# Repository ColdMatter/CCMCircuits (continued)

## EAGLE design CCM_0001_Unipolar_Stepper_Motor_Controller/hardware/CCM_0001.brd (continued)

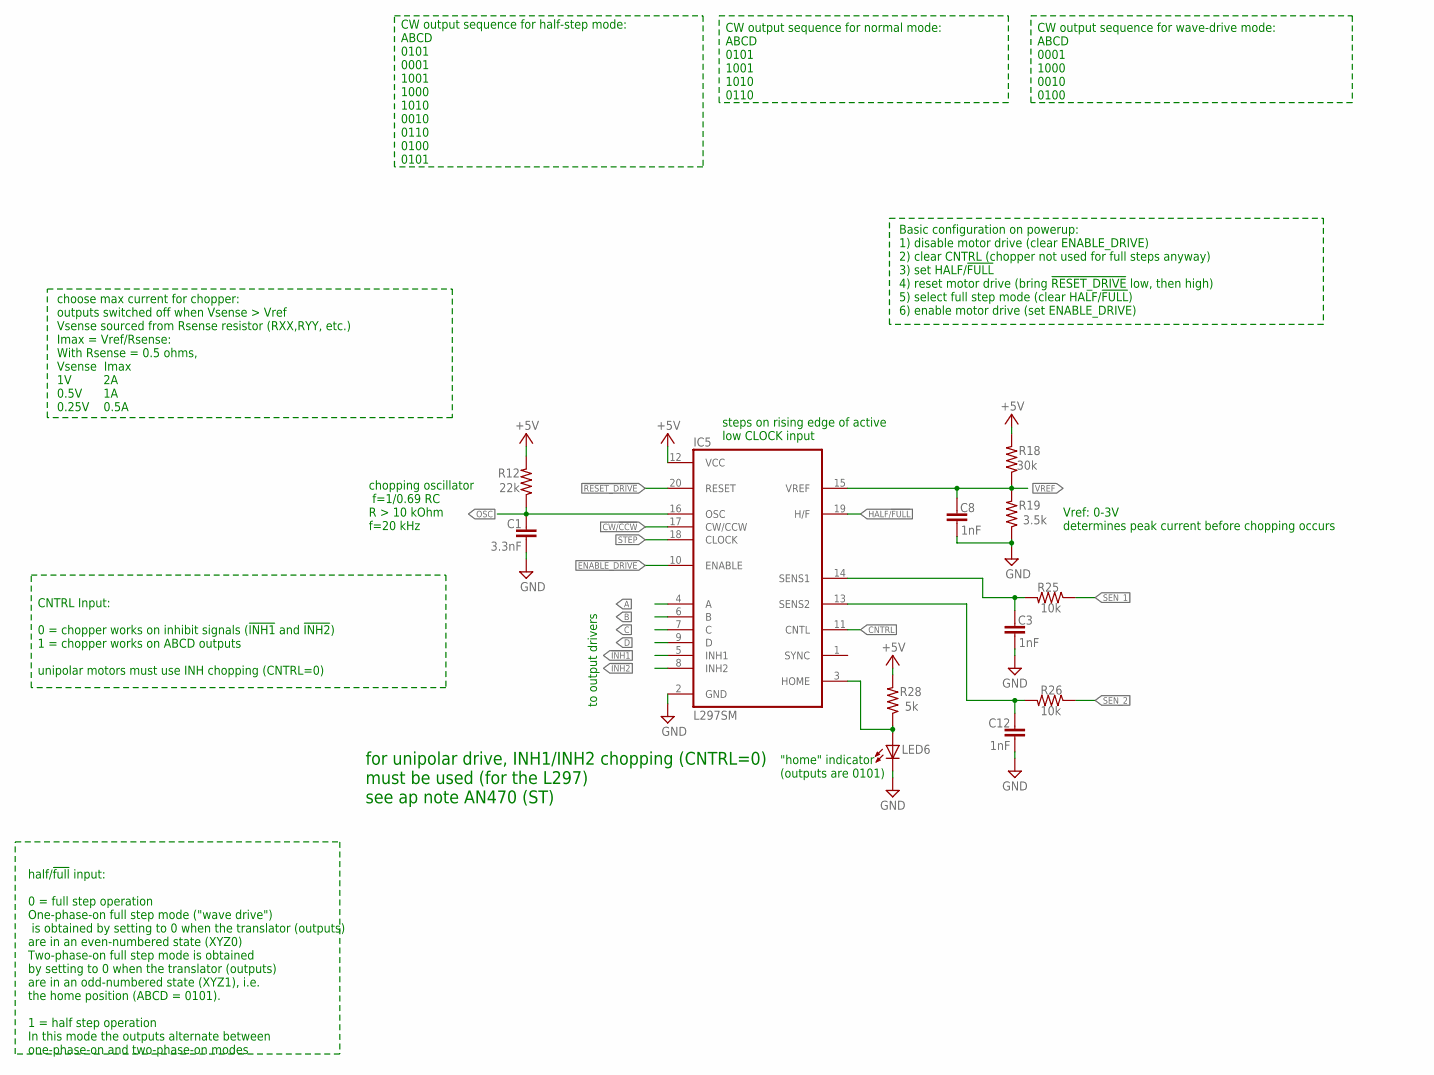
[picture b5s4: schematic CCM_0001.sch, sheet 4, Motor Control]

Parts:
C1: 3.3nF; 0603-CAP
C3, C8, C12: 1nF; 0603-CAP
IC5: L297SM; SO20
LED6: red; CHIPLED_0603
R12: 22k; 0603-RES
R18: 30k; 0603-RES
R19: 3.5k; 0603-RES
R25, R26: 10k; 0603-RES
R28: 5k; 0603-RES

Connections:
!INH1: IC5.5 (INH1); also elsewhere on the board
!INH2: IC5.8 (INH2); also elsewhere on the board
!RESET_DRIVE: IC5.20 (RESET); also elsewhere on the board
+5V: IC5.12 (VCC), R12.2, R18.2, R28.2; also elsewhere on the board
A: IC5.4 (A); also elsewhere on the board
B: IC5.6 (B); also elsewhere on the board
C: IC5.7 (C); also elsewhere on the board
CNTRL: IC5.11 (CNTL); also elsewhere on the board
CW/!CCW: IC5.17 (CW/CCW); also elsewhere on the board
D: IC5.9 (D); also elsewhere on the board
ENABLE_DRIVE: IC5.10 (ENABLE); also elsewhere on the board
GND: C1.2, C3.2, C8.2, C12.2, IC5.2 (GND), LED6.C, R19.1; also elsewhere on the board
HALF/!FULL: IC5.19 (H/F); also elsewhere on the board
unnamed: IC5.3 (HOME), LED6.A, R28.1
OSC: C1.1, IC5.16 (OSC), R12.1
SENSE1: C3.1, IC5.14 (SENS1), R25.2
SENSE2: C12.1, IC5.13 (SENS2), R26.2
SEN_1: R25.1; also elsewhere on the board
SEN_2: R26.1; also elsewhere on the board
STEP: IC5.18 (CLOCK); also elsewhere on the board
VREF: C8.1, IC5.15 (VREF), R18.1, R19.2

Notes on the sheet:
chopping oscillator f=1/0.69 RC R > 10 kOhm f=20 kHz
steps on rising edge of active low CLOCK input
choose max current for chopper: outputs switched off when Vsense > Vref Vsense sourced from Rsense resistor (RXX,RYY, etc.) Imax = Vref/Rsense: With Rsense = 0.5 ohms, Vsense Imax 1V 2A 0.5V 1A 0.25V 0.5A
"home" indicator (outputs are 0101)
to output drivers
CNTRL Input: 0 = chopper works on inhibit signals (!INH1! and !INH2!) 1 = chopper works on ABCD outputs unipolar motors must use INH chopping (CNTRL=0)
half/!full! input: 0 = full step operation One-phase-on full step mode ("wave drive") is obtained by setting to 0 when the translator (outputs) are in an even-numbered state (XYZ0) Two-phase-on full step mode is obtained by setting to 0 when the translator (outputs) are in an odd-numbered state (XY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
CW output sequence for half-step mode: ABCD 0101 0001 1001 1000 1010 0010 0110 0100 0101
Basic configuration on powerup: 1) disable motor drive (clear ENABLE_DRIVE) 2) clear CNTRL (chopper not used for full steps anyway) 3) set HALF/!FULL! 4) reset motor drive (bring !RESET_DRIVE! low, then high) 5) select full step mode (clear HALF/!FULL!) 6) enable motor drive (set ENABLE_DRIVE)
CW output sequence for normal mode: ABCD 0101 1001 1010 0110
CW output sequence for wave-drive mode: ABCD 0001 1000 0010 0100
Vref: 0-3V determines peak current before chopping occurs
for unipolar drive, INH1/INH2 chopping (CNTRL=0) must be used (for the L297) see ap note AN470 (ST)

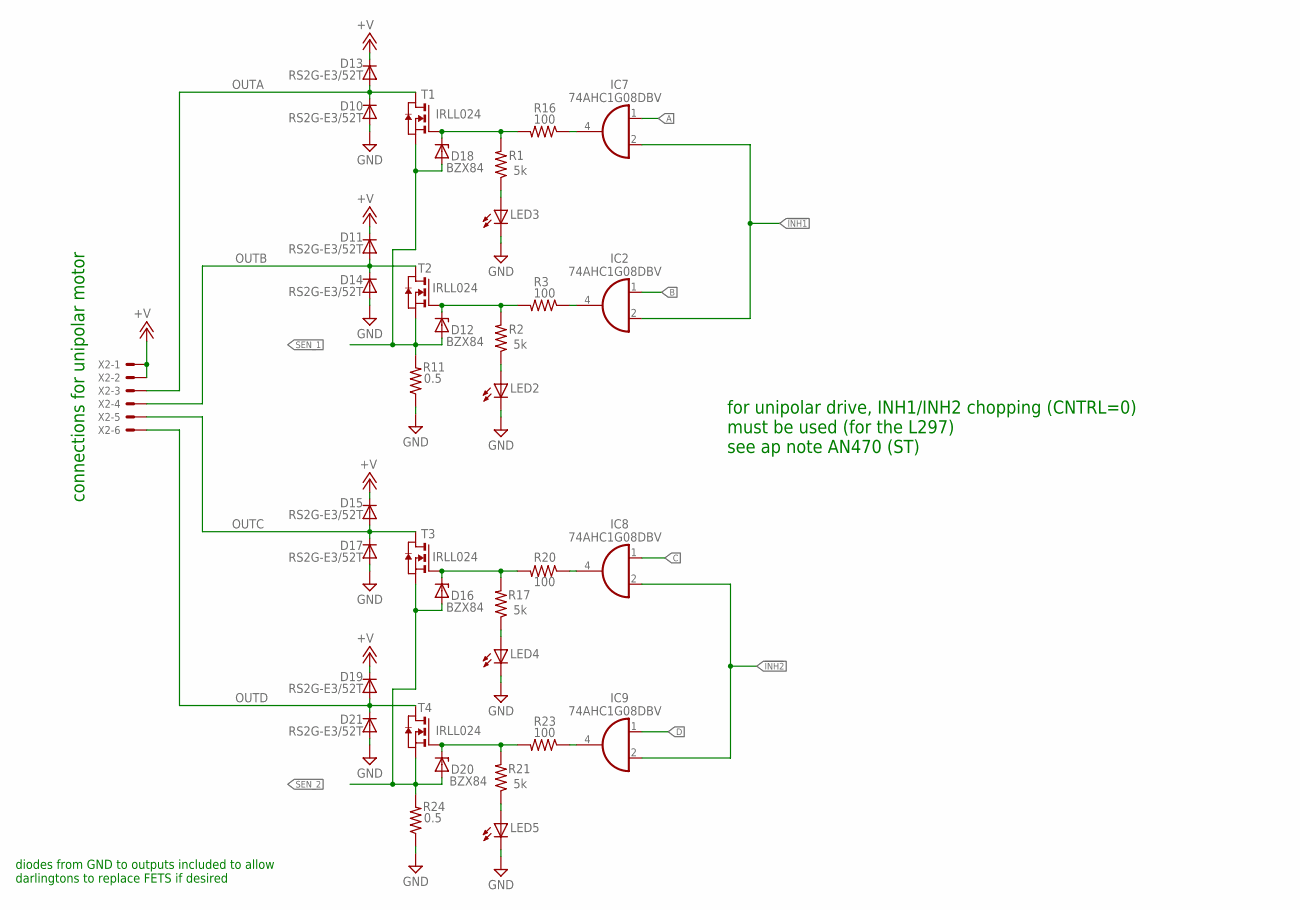
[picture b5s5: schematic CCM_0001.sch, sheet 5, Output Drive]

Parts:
D10, D11, D13, D14, D15, D17, D19, D21: RS2G-E3/52T; DO214AA
D12, D16, D18, D20: BZX84; SOT23
IC2, IC7, IC8, IC9: 74AHC1G08DBV; SOT23-5
LED2, LED3, LED4, LED5: red; CHIPLED_0603
R1, R2, R17, R21: 5k; 0603-RES
R3, R16, R20, R23: 100; 0603-RES
R11, R24: 0.5; R2512
T1, T2, T3, T4: IRLL024; SOT223
X2: 22-23-2061

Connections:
!INH1: IC2.2 (I1), IC7.2 (I1); also elsewhere on the board
!INH2: IC8.2 (I1), IC9.2 (I1); also elsewhere on the board
+V: D11.C, D13.C, D15.C, D19.C, X2.1, X2.2; also elsewhere on the board
A: IC7.1 (I0); also elsewhere on the board
B: IC2.1 (I0); also elsewhere on the board
C: IC8.1 (I0); also elsewhere on the board
D: IC9.1 (I0); also elsewhere on the board
GND: D10.A, D14.A, D17.A, D21.A, LED2.C, LED3.C, LED4.C, LED5.C, R11.1, R24.1; also elsewhere on the board
unnamed: LED2.A, R2.1
unnamed: D12.3 (C), R2.2, R3.2, T2.1 (G)
unnamed: IC2.4 (O), R3.1
unnamed: LED4.A, R17.1
unnamed: D16.3 (C), R17.2, R20.2, T3.1 (G)
unnamed: IC8.4 (O), R20.1
unnamed: LED5.A, R21.1
unnamed: D20.3 (C), R21.2, R23.2, T4.1 (G)
unnamed: IC9.4 (O), R23.1
unnamed: D18.3 (C), R1.2, R16.2, T1.1 (G)
unnamed: LED3.A, R1.1
unnamed: IC7.4 (O), R16.1
OUTA: D10.C, D13.A, T1.2 (D), T1.4 (D), X2.3
OUTB: D11.A, D14.C, T2.2 (D), T2.4 (D), X2.4
OUTC: D15.A, D17.C, T3.2 (D), T3.4 (D), X2.5
OUTD: D19.A, D21.C, T4.2 (D), T4.4 (D), X2.6
SEN_1: D12.1 (A), D18.1 (A), R11.2, T1.3 (S), T2.3 (S); also elsewhere on the board
SEN_2: D16.1 (A), D20.1 (A), R24.2, T3.3 (S), T4.3 (S); also elsewhere on the board

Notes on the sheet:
connections for unipolar motor
diodes from GND to outputs included to allow darlingtons to replace FETS if desired
for unipolar drive, INH1/INH2 chopping (CNTRL=0) must be used (for the L297) see ap note AN470 (ST)

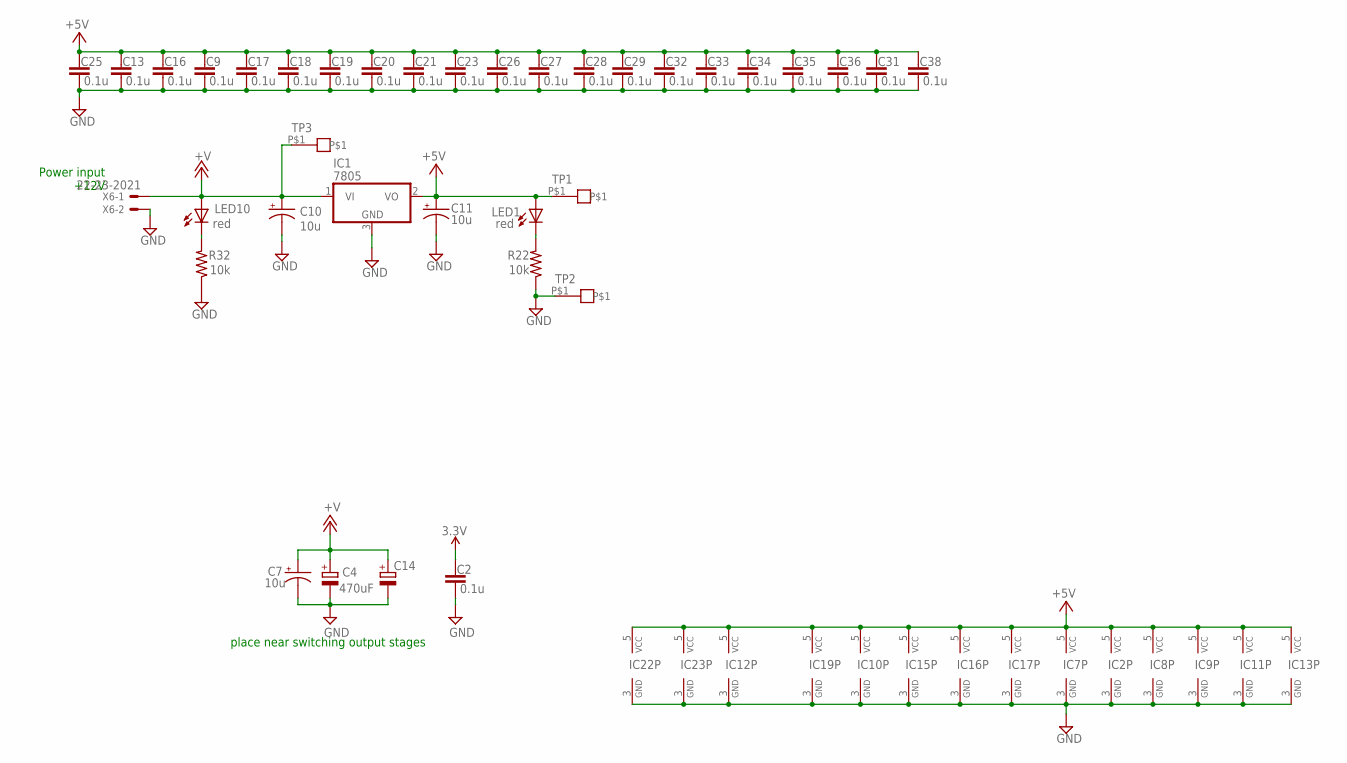
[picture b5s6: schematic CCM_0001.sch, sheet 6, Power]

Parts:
C2, C9, C13, C16, C17, C18, C19, C20, C21, C23, C25, C26, C27, C28, C29, C31, C32, C33, C34, C35, C36, C38: 0.1u; 0603-CAP
C4: 470uF; SANYO-OSCON_SMD_F8
C7, C10, C11: 10u; EIA3216
C14: CPOL-EUE5-13; E5-13
IC1: 7805; TO252
IC2, IC7, IC8, IC9, IC11, IC13, IC19: 74AHC1G08DBV; SOT23-5
IC10, IC16: 74HC1G125; SOT23-5
IC12: 74HC1G04; SOT23-5
IC15, IC17: 74HC1G126; SOT23-5
IC22, IC23: 74HC1G08; SOT23-5
LED1, LED10: red; CHIPLED_0603
R22, R32: 10k; 0603-RES
TP1, TP2, TP3: TESTPOINT
X6: 22-23-2021

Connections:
3.3V: C2.1; also elsewhere on the board
+5V: C9.1, C11.A (+), C13.1, C16.1, C17.1, C18.1, C19.1, C20.1, C21.1, C23.1, C25.1, C26.1, C27.1, C28.1, C29.1, C31.1, C32.1, C33.1, C34.1, C35.1, C36.1, C38.1, IC1.2 (VO), IC2.5 (VCC), IC7.5 (VCC), IC8.5 (VCC), IC9.5 (VCC), IC10.5 (VCC), IC11.5 (VCC), IC12.5 (VCC), IC13.5 (VCC), IC15.5 (VCC), IC16.5 (VCC), IC17.5 (VCC), IC19.5 (VCC), IC22.5 (VCC), IC23.5 (VCC), LED1.A, TP1.P$1; also elsewhere on the board
+V: C4.+, C7.A (+), C10.A (+), C14.+, IC1.1 (VI), LED10.A, TP3.P$1, X6.1; also elsewhere on the board
GND: C2.2, C4.-, C7.C (-), C9.2, C10.C (-), C11.C (-), C13.2, C14.-, C16.2, C17.2, C18.2, C19.2, C20.2, C21.2, C23.2, C25.2, C26.2, C27.2, C28.2, C29.2, C31.2, C32.2, C33.2, C34.2, C35.2, C36.2, C38.2, IC1.3 (GND), IC2.3 (GND), IC7.3 (GND), IC8.3 (GND), IC9.3 (GND), IC10.3 (GND), IC11.3 (GND), IC12.3 (GND), IC13.3 (GND), IC15.3 (GND), IC16.3 (GND), IC17.3 (GND), IC19.3 (GND), IC22.3 (GND), IC23.3 (GND), R22.1, R32.1, TP2.P$1, X6.2; also elsewhere on the board
LED1: LED1.C, R22.2
LED5: LED10.C, R32.2

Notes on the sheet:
Power input +12V
place near switching output stages

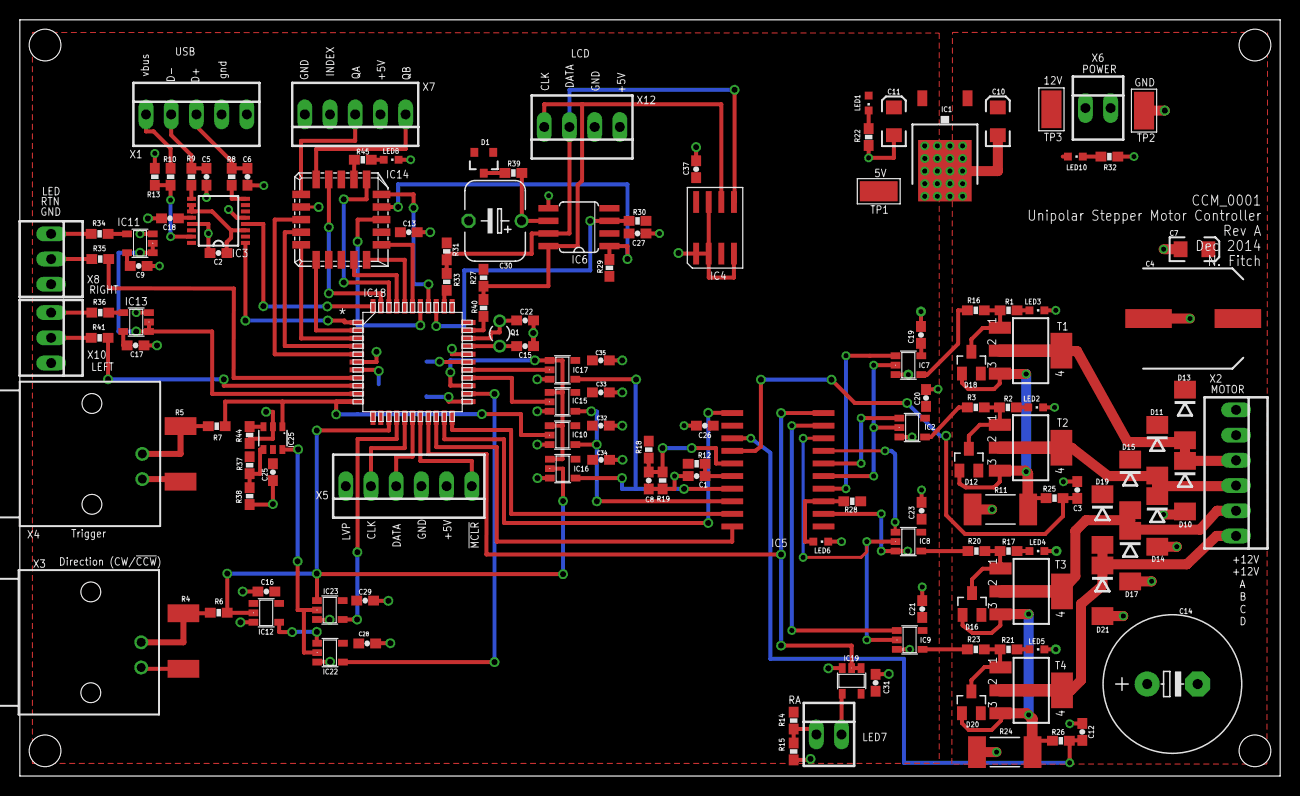
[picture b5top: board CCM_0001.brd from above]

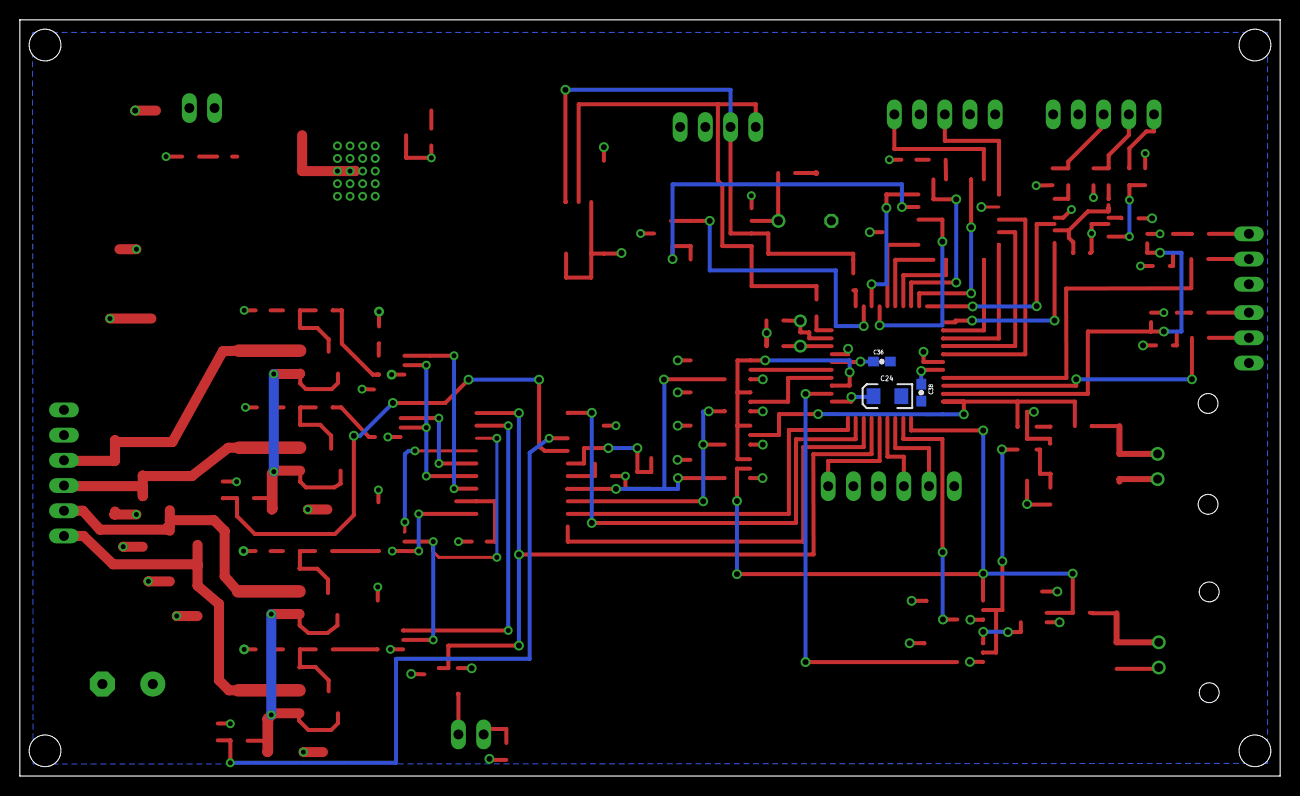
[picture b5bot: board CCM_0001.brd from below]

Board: 2 copper layers, 127.0 x 76.2 mm, 143 parts (3 on the bottom side), 102 nets.

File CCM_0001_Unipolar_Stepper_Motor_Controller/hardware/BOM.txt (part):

Partlist exported from C:/Users/nfitch/Google Drive/Electronics/Projects/CCM_0001_Unipolar_Stepper_Motor_Controller/RevA/Circuit/Unipolar_Stepper_Motor_Controller_RevA.sch at 06/01/2015 10:42:07

Qty Value        Device              Package            Parts                                                                                                           Description                                           MF               MPN         OC_FARNELL OC_NEWARK
2                22-23-2061          22-23-2061         X2, X5                                                                                                          .100" (2.54mm) Center Header - 6 Pin                  MOLEX            22-23-2061  1462922    27C1933  
1                BILED               22-23-2021         LED7                                                                                                            DUO LED                                                                                                
1                CPOL-EUE5-13        E5-13              C14                                                                                                             POLARIZED CAPACITOR, European symbol                                                                   
1   0            RESISTOR0603-RES    0603-RES           R38                                                                                                             Resistor                                                                                               
1   0.1F         CPOL-USP128-60      P128-60            C30                                                                                                             POLARIZED CAPACITOR, American symbol                                                                   
23  0.1u         CAP0603-CAP         0603-CAP           C2, C9, C13, C16, C17, C18, C19, C20, C21, C23, C25, C26, C27, C28, C29, C31, C32, C33, C34, C35, C36, C37, C38 Capacitor                                                                                              
2   0.5          R-US_R2512          R2512              R11, R24                                                                                                        RESISTOR, American symbol                                                                              
2   1-227161-0   1-227161-0          AMP_227161         X3, X4                                                                                                          JACK,  RIGHT ANGLE, 50 OHM, PCB, BNC                  TYCO ELECTRONICS 1-227161    unknown    33B3200  
6   100          RESISTOR0603-RES    0603-RES           R3, R16, R20, R23, R33, R40                                                                                     Resistor                                                                                               
8   10k          RESISTOR0603-RES    0603-RES           R13, R22, R25, R26, R29, R30, R32, R39                                                                          Resistor                                                                                               
4   10u          CAP_POL1206         EIA3216            C7, C10, C11, C24                                                                                               Capacitor Polarized                                                                                    
7   1k           RESISTOR0603-RES    0603-RES           R6, R7, R14, R15, R19, R35, R41                                                                                 Resistor                                                                                               
3   1nF          CAP0603-CAP         0603-CAP           C3, C8, C12                                                                                                     Capacitor                                                                                              
1   20MHz        CRYSTALTC26V        TC26V              Q1                                                                                                              CRYSTAL                                                                                                
1   22-23-2021   22-23-2021          22-23-2021         X6                                                                                                              .100" (2.54mm) Center Header - 2 Pin                  MOLEX            22-23-2021  1462926    25C3832  
2   22-23-2031   22-23-2031          22-23-2031         X8, X10                                                                                                         .100" (2.54mm) Center Header - 3 Pin                  MOLEX            22-23-2031  1462950    30C0862  
1   22-23-2041   22-23-2041          22-23-2041         X12                                                                                                             .100" (2.54mm) Center Header - 4 Pin                  MOLEX            22-23-2041  1462920    38C0355  
2   22-23-2051   22-23-2051          22-23-2051         X1, X7                                                                                                          .100" (2.54mm) Center Header - 5 Pin                  MOLEX            22-23-2051  1462952    38C9178  
1   22k          RESISTOR0603-RES    0603-RES           R12                                                                                                             Resistor                                                                                               
2   22p          CAP0603-CAP         0603-CAP           C15, C22                                                                                                        Capacitor                                                                                              
1   24AA1025     24AA16SN            SO-08              IC4                                                                                                             Serial EEPROM                                         MICROCHIP        24AA16-I/SN 1331289    96K4056  
2   27           RESISTOR0603-RES    0603-RES           R8, R9                                                                                                          Resistor                                                                                               
1   3.3nF        CAP0603-CAP         0603-CAP           C1                                                                                                              Capacitor                                                                                              
2   300          RESISTOR0603-RES    0603-RES           R34, R36                                                                                                        Resistor                                                                                               
1   30k          RESISTOR0603-RES    0603-RES           R18                                                                                                             Resistor                                                                                               
3   4.7k         RESISTOR0603-RES    0603-RES           R10, R27, R31                                                                                                   Resistor                                                                                               
1   4148         DIODESOT23          SOT23-3            D1                                                                                                              Diode                                                                                                  
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
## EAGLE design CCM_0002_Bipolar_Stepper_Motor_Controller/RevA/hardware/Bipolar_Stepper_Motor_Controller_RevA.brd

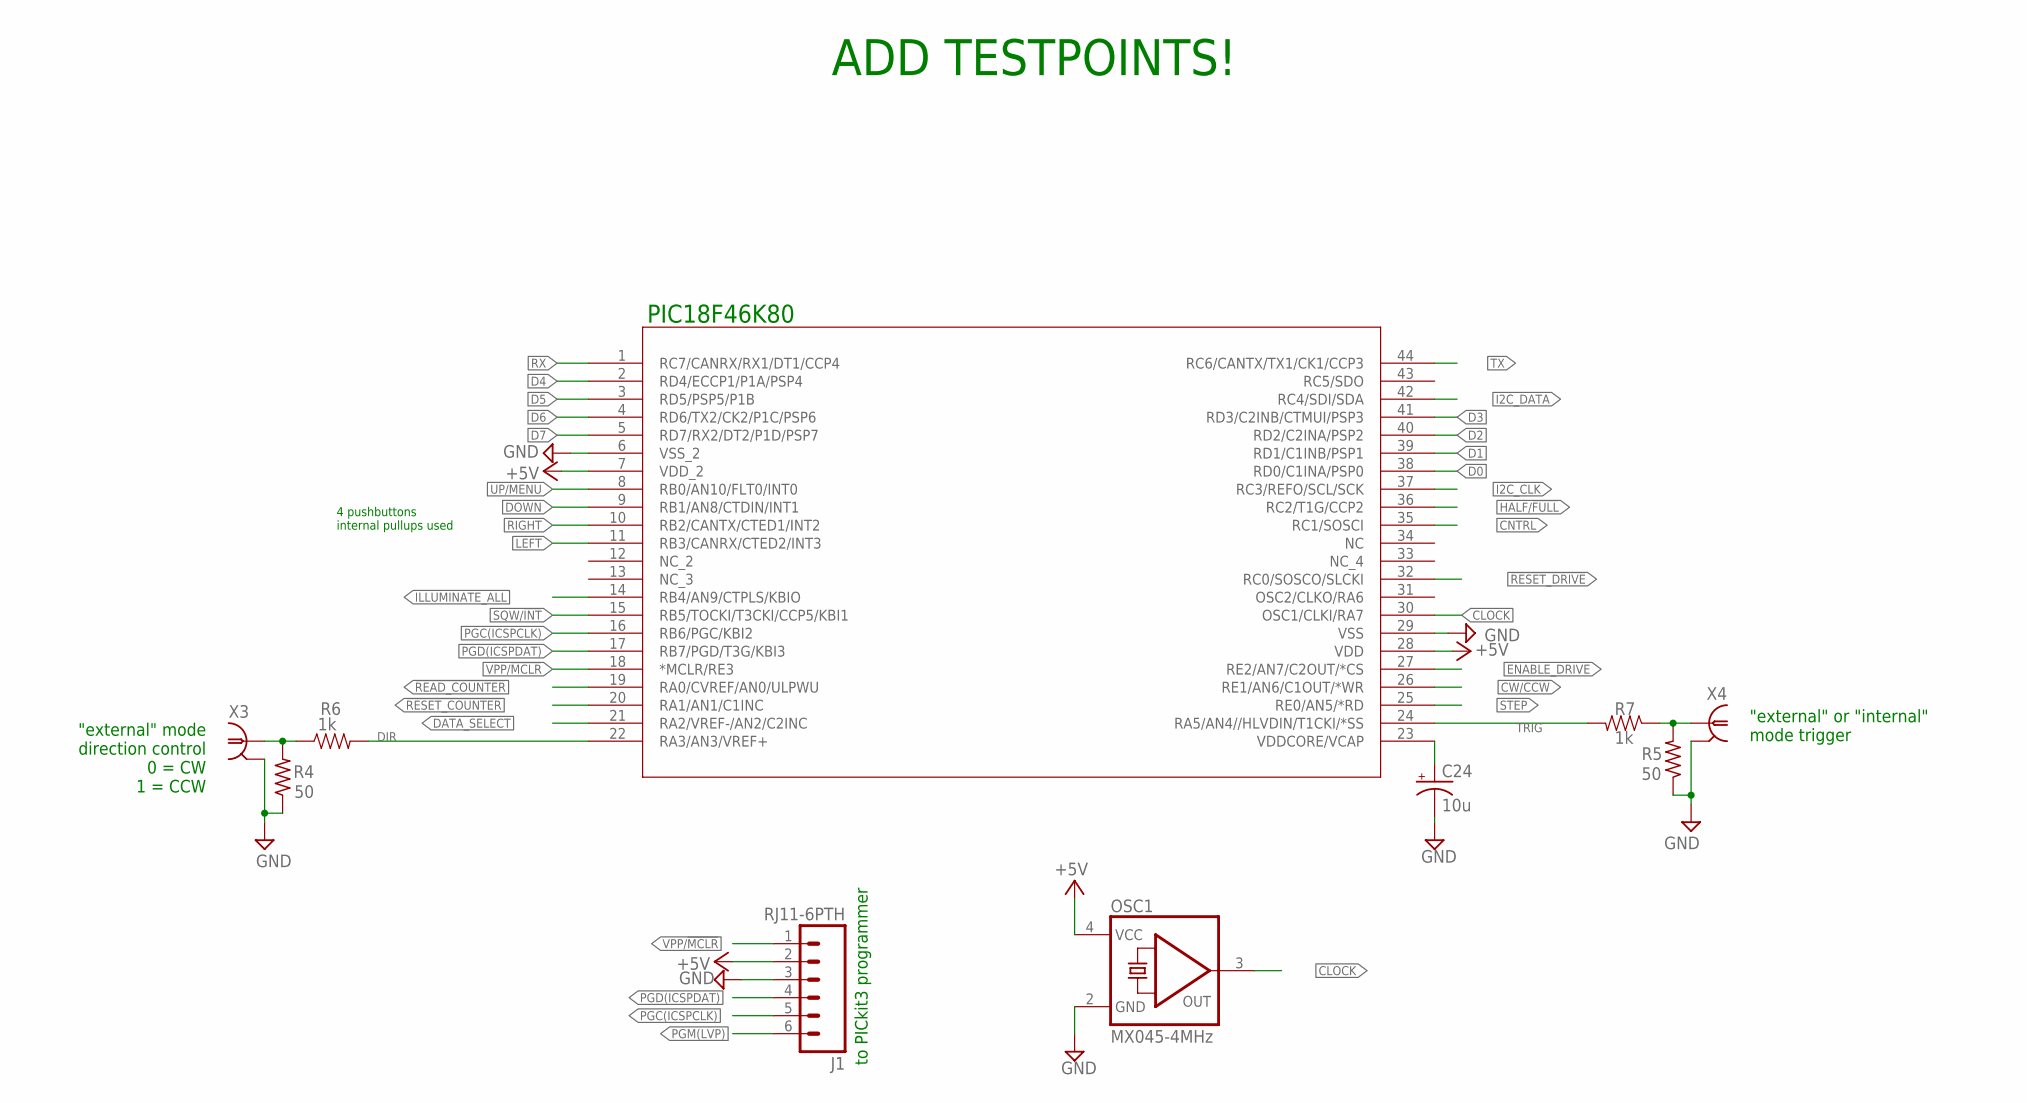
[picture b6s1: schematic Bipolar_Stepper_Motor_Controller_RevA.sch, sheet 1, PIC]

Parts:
C24: 10u; EIA3216
IC12: PIC18F46K80; TQFP44_MC
J1: RJ11-6PTH; RJ11-6
OSC1: MX045-4MHz; DIL08-4
R4, R5: 50; R2512
R6, R7: 1k; 0805
X3, X4: 1-227161-0; AMP_227161

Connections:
!READ_COUNTER: IC12.19 (RA0/CVREF/AN0/ULPWU); also elsewhere on the board
!RESET_COUNTER: IC12.20 (RA1/AN1/C1INC); also elsewhere on the board
!RESET_DRIVE: IC12.32 (RC0/SOSCO/SLCKI); also elsewhere on the board
+5V: IC12.7 (VDD_2), IC12.28 (VDD), J1.2, OSC1.4 (VCC); also elsewhere on the board
CLOCK: IC12.30 (OSC1/CLKI/RA7), OSC1.3 (OUT); also elsewhere on the board
CNTRL: IC12.35 (RC1/SOSCI); also elsewhere on the board
CW/!CCW: IC12.26 (RE1/AN6/C1OUT/*WR); also elsewhere on the board
D0: IC12.38 (RD0/C1INA/PSP0); also elsewhere on the board
D1: IC12.39 (RD1/C1INB/PSP1); also elsewhere on the board
D2: IC12.40 (RD2/C2INA/PSP2); also elsewhere on the board
D3: IC12.41 (RD3/C2INB/CTMUI/PSP3); also elsewhere on the board
D4: IC12.2 (RD4/ECCP1/P1A/PSP4); also elsewhere on the board
D5: IC12.3 (RD5/PSP5/P1B); also elsewhere on the board
D6: IC12.4 (RD6/TX2/CK2/P1C/PSP6); also elsewhere on the board
D7: IC12.5 (RD7/RX2/DT2/P1D/PSP7); also elsewhere on the board
DATA_SELECT: IC12.21 (RA2/VREF-/AN2/C2INC); also elsewhere on the board
DIR: IC12.22 (RA3/AN3/VREF+), R6.2
DOWN: IC12.9 (RB1/AN8/CTDIN/INT1); also elsewhere on the board
ENABLE_DRIVE: IC12.27 (RE2/AN7/C2OUT/*CS); also elsewhere on the board
GND: C24.C (-), IC12.6 (VSS_2), IC12.29 (VSS), J1.3, OSC1.2 (GND), R4.1, R5.1, X3.2, X4.2; also elsewhere on the board
HALF/!FULL: IC12.36 (RC2/T1G/CCP2); also elsewhere on the board
I2C_CLK: IC12.37 (RC3/REFO/SCL/SCK); also elsewhere on the board
I2C_DATA: IC12.42 (RC4/SDI/SDA); also elsewhere on the board
ILLUMINATE_ALL: IC12.14 (RB4/AN9/CTPLS/KBIO); also elsewhere on the board
LEFT: IC12.11 (RB3/CANRX/CTED2/INT3); also elsewhere on the board
unnamed: R5.2, R7.1, X4.1
unnamed: R4.2, R6.1, X3.1
unnamed: C24.A (+), IC12.23 (VDDCORE/VCAP)
PGC(ICSPCLK): IC12.16 (RB6/PGC/KBI2), J1.5
PGD(ICSPDAT): IC12.17 (RB7/PGD/T3G/KBI3), J1.4
PGM(LVP): J1.6
RIGHT: IC12.10 (RB2/CANTX/CTED1/INT2); also elsewhere on the board
RX: IC12.1 (RC7/CANRX/RX1/DT1/CCP4); also elsewhere on the board
SQW/!INT: IC12.15 (RB5/TOCKI/T3CKI/CCP5/KBI1); also elsewhere on the board
STEP: IC12.25 (RE0/AN5/*RD); also elsewhere on the board
TRIG: IC12.24 (RA5/AN4//HLVDIN/T1CKI/*SS), R7.2
TX: IC12.44 (RC6/CANTX/TX1/CK1/CCP3); also elsewhere on the board
UP/MENU: IC12.8 (RB0/AN10/FLT0/INT0); also elsewhere on the board
VPP/!MCLR: IC12.18 (*MCLR/RE3), J1.1

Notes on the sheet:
PIC18F46K80
to PICkit3 programmer
"external" mode direction control 0 = CW 1 = CCW
"external" or "internal" mode trigger
4 pushbuttons internal pullups used
ADD TESTPOINTS!

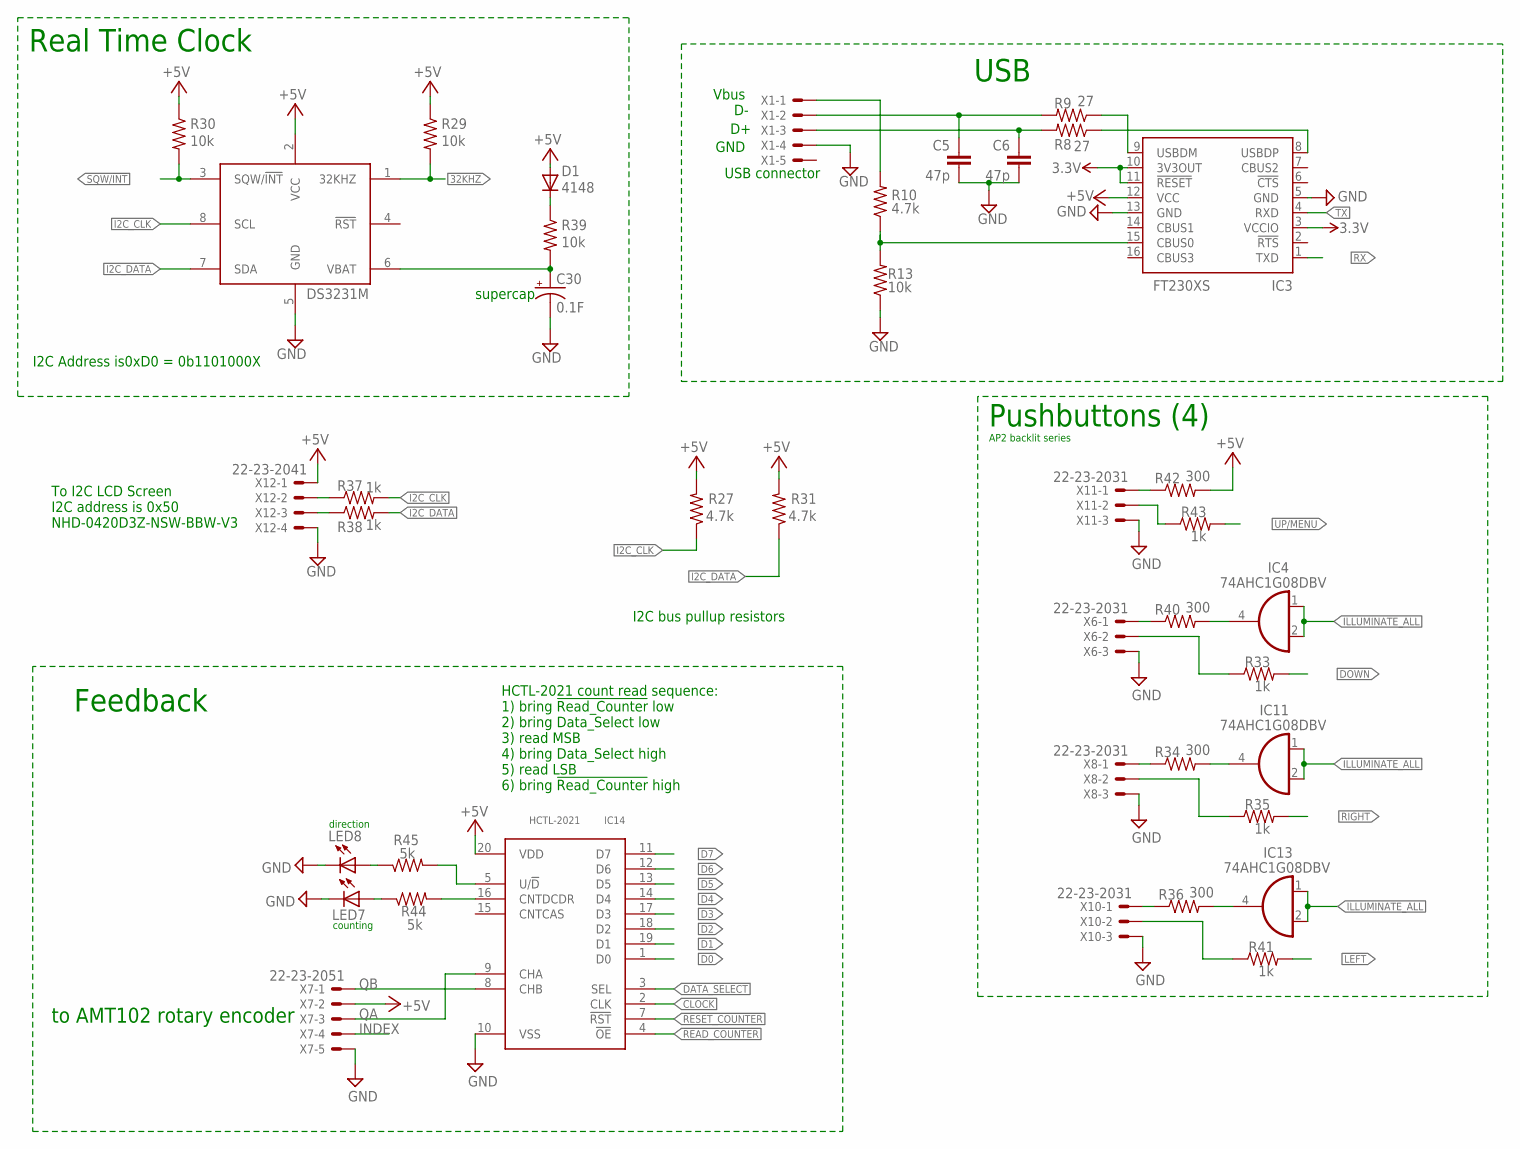
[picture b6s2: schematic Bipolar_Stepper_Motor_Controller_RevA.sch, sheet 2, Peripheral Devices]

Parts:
C5, C6: 47p; 0805
C30: 0.1F; P128-60
D1: 4148; SOT23-3
IC3: FT230XS; SSOP16
IC4, IC11, IC13: 74AHC1G08DBV; SOT23-5
IC6: DS3231M; 8-SOIC
IC14: HCTL-2021; PLCC20
LED7, LED8: red; CHIPLED_0603
R8, R9: 27; 0805
R10: 4.7k; 0805
R13: 10k; 0805
R27, R31: 4.7k; 0603-RES
R29, R30, R39: 10k; 0603-RES
R33, R35, R37, R38, R41, R43: 1k; 0805
R34, R36, R40, R42: 300; 0805
R44, R45: 5k; 0603-RES
X1, X7: 22-23-2051
X6, X8, X10, X11: 22-23-2031
X12: 22-23-2041

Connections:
3.3V: IC3.3 (VCCIO), IC3.10 (3V3OUT), IC3.11 (!RESET); also elsewhere on the board
32KHZ: IC6.1 (32KHZ), R29.2
!READ_COUNTER: IC14.4 (!OE); also elsewhere on the board
!RESET_COUNTER: IC14.7 (!RST); also elsewhere on the board
+5V: D1.1 (A), IC3.12 (VCC), IC6.2 (VCC), IC14.20 (VDD), R27.2, R29.1, R30.1, R31.2, R42.2, X7.2, X12.1; also elsewhere on the board
CLOCK: IC14.2 (CLK); also elsewhere on the board
D0: IC14.1 (D0); also elsewhere on the board
D1: IC14.19 (D1); also elsewhere on the board
D2: IC14.18 (D2); also elsewhere on the board
D3: IC14.17 (D3); also elsewhere on the board
D4: IC14.14 (D4); also elsewhere on the board
D5: IC14.13 (D5); also elsewhere on the board
D6: IC14.12 (D6); also elsewhere on the board
D7: IC14.11 (D7); also elsewhere on the board
D+: C6.1, R8.2, X1.3
D-: C5.1, R9.2, X1.2
DATA_SELECT: IC14.3 (SEL); also elsewhere on the board
DOWN: R33.2; also elsewhere on the board
GND: C5.2, C6.2, C30.-, IC3.5 (GND), IC3.13 (GND), IC6.5 (GND), IC14.10 (VSS), LED7.C, LED8.C, R13.1, X1.4, X6.3, X7.5, X8.3, X10.3, X11.3, X12.4; also elsewhere on the board
I2C_CLK: IC6.8 (SCL), R27.1, R37.2; also elsewhere on the board
I2C_DATA: IC6.7 (SDA), R31.1, R38.2; also elsewhere on the board
ILLUMINATE_ALL: IC4.1 (I0), IC4.2 (I1), IC11.1 (I0), IC11.2 (I1), IC13.1 (I0), IC13.2 (I1); also elsewhere on the board
INDEX: X7.4
LEFT: R41.2; also elsewhere on the board
unnamed: D1.3 (C), R39.1
unnamed: IC3.9 (USBDM), R9.1
unnamed: IC3.8 (USBDP), R8.1
unnamed: IC3.15 (CBUS0), R10.1, R13.2
unnamed: C30.+, IC6.6 (VBAT), R39.2
unnamed: R40.1, X6.1
unnamed: IC4.4 (O), R40.2
unnamed: R33.1, X6.2
unnamed: R34.1, X8.1
unnamed: R37.1, X12.2
unnamed: R38.1, X12.3
unnamed: IC11.4 (O), R34.2
unnamed: R35.1, X8.2
unnamed: R36.1, X10.1
unnamed: IC13.4 (O), R36.2
unnamed: R41.1, X10.2
unnamed: R42.1, X11.1
unnamed: R43.1, X11.2
unnamed: LED7.A, R44.1
unnamed: IC14.16 (CNTDCDR), R44.2
unnamed: LED8.A, R45.1
unnamed: IC14.5 (U/!D), R45.2
QA: IC14.9 (CHA), X7.3
QB: IC14.8 (CHB), X7.1
RIGHT: R35.2; also elsewhere on the board
RX: IC3.1 (TXD); also elsewhere on the board
SQW/!INT: IC6.3 (SQW/!INT), R30.2; also elsewhere on the board
TX: IC3.4 (RXD); also elsewhere on the board
UP/MENU: R43.2; also elsewhere on the board
VBUS: R10.2, X1.1

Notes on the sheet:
USB connector
I2C Address is0xD0 = 0b1101000X
supercap
Real Time Clock
USB
To I2C LCD Screen I2C address is 0x50 NHD-0420D3Z-NSW-BBW-V3
I2C bus pullup resistors
to AMT102 rotary encoder
HCTL-2021 count read sequence: 1) bring !Read_Counter! low 2) bring Data_Select low 3) read MSB 4) bring Data_Select high 5) read LSB 6) bring !Read_Counter! high
counting
direction
Feedback
Pushbuttons (4)
AP2 backlit series
Vbus
GND
